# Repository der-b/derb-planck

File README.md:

# derb-planck

DIY mechanical keyboard which can be connected to several hosts at the same time.
[See blog post for more details.](https://der-b.com/posts/2024-05-08-mechanical-keyboard-derb-planck/)

## PCB

The PCB is designed with KiCad and is located in the subdirectory "PCB".

## Case

The Case is designed with FreeCAD and is located in the subdirectory "case".

## Firmeware

[This keyboard uses QMK as firmware.](https://github.com/der-b/qmk_firmware/tree/derb_planck/keyboards/handwired/derb_planck)

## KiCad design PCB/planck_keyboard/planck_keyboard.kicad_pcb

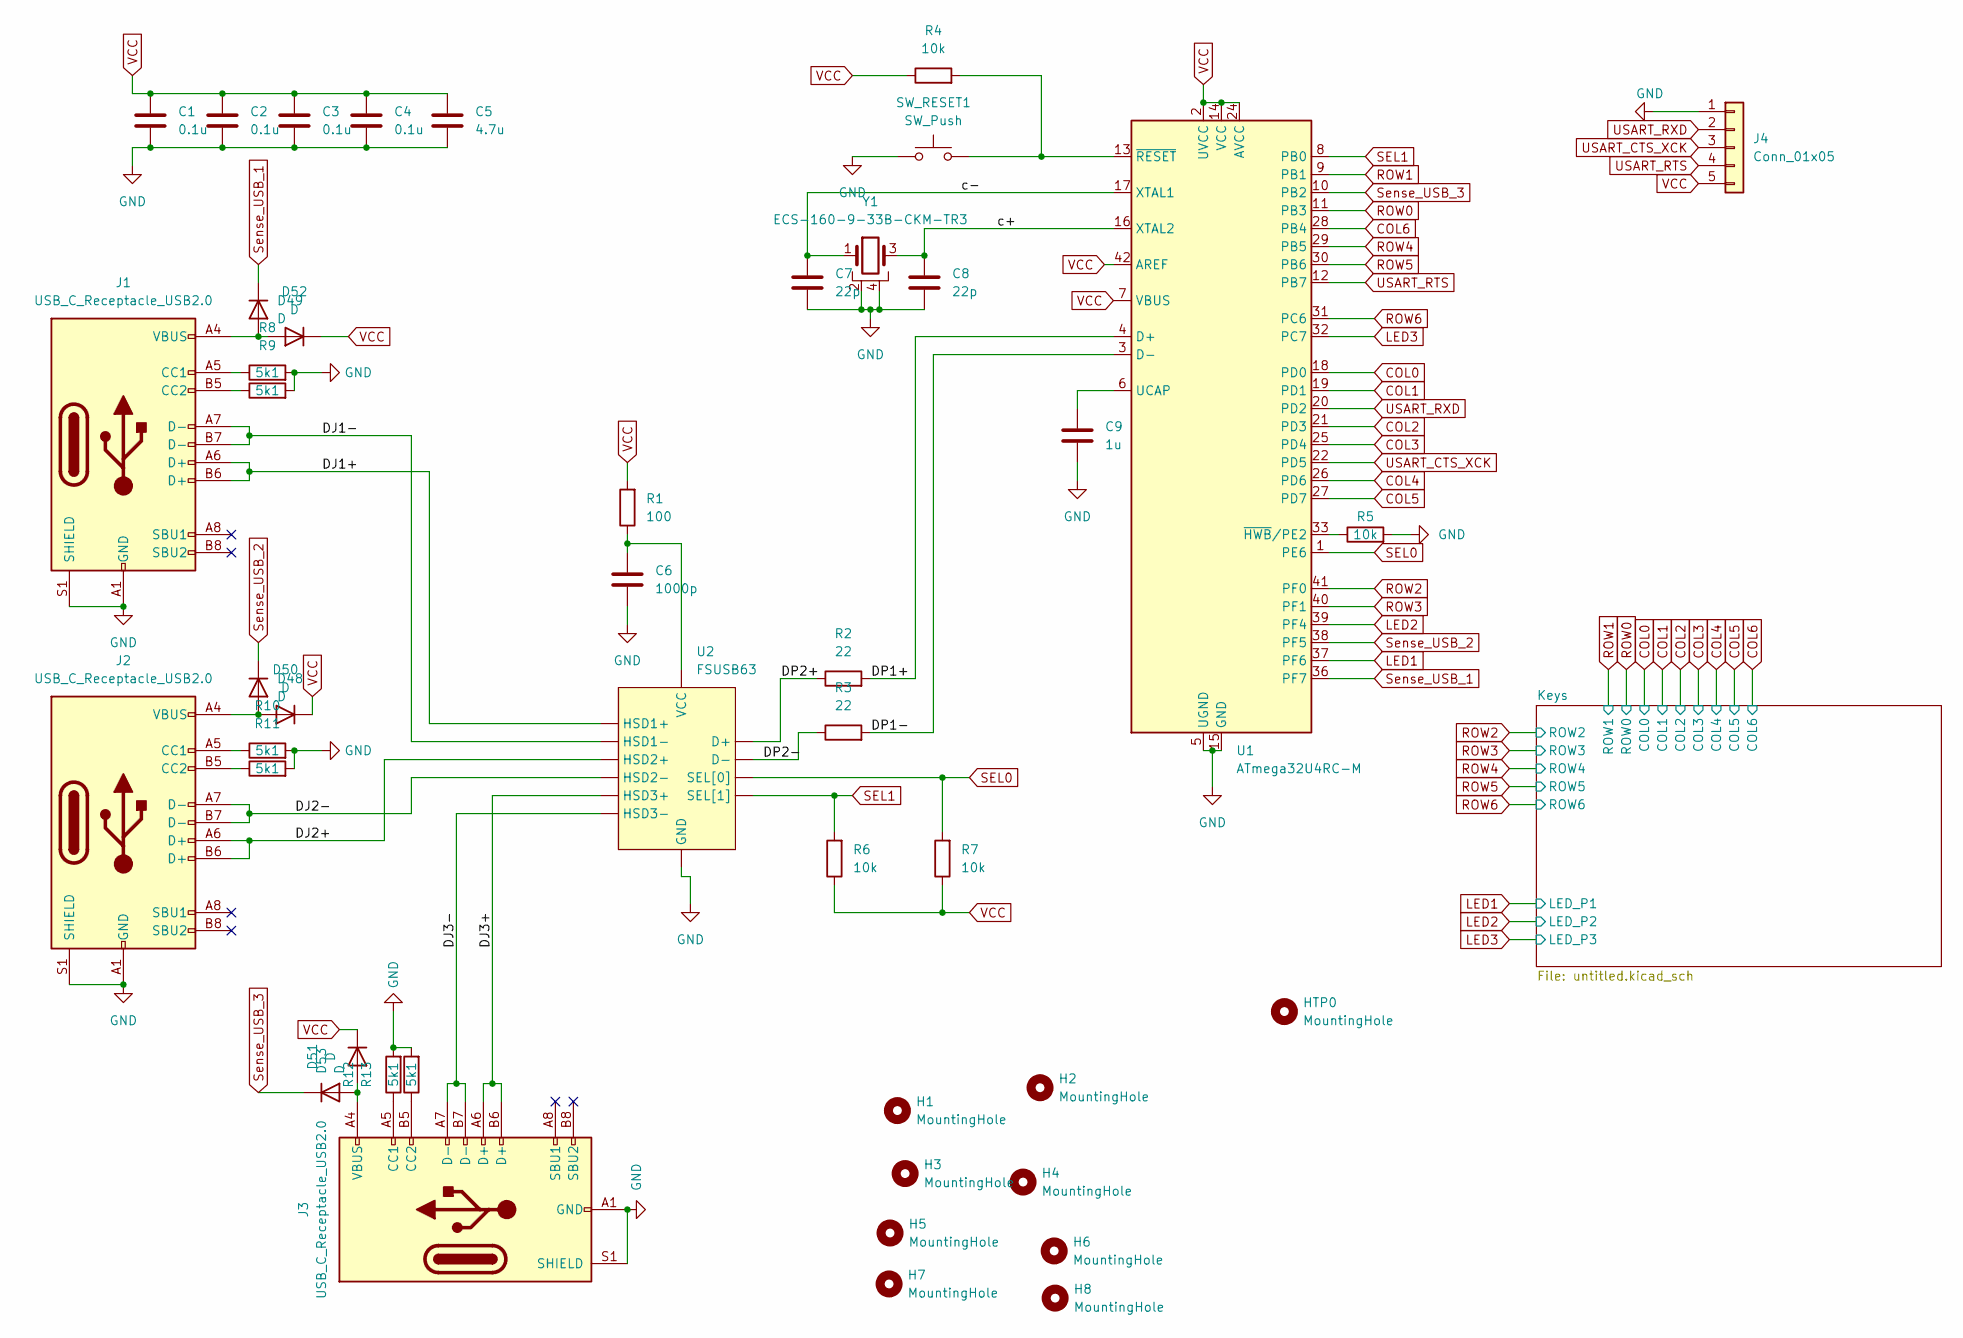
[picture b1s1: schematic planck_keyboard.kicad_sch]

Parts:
C1, C2, C3, C4: 0.1u; C_0603_1608Metric_Pad1.08x0.95mm_HandSolder
C5: 4.7u; C_0603_1608Metric_Pad1.08x0.95mm_HandSolder
C6: 1000p; C_0603_1608Metric_Pad1.08x0.95mm_HandSolder
C7, C8: 22p; C_0603_1608Metric_Pad1.08x0.95mm_HandSolder
C9: 1u; C_0603_1608Metric_Pad1.08x0.95mm_HandSolder
D48, D49, D50, D51, D52, D53: D; D_SOD-523
H1, H2, H3, H4, H5, H6, H7, H8: MountingHole; MountingHole_3.2mm_M3
HTP0: MountingHole; MountingHole_3.5mm
J1, J2, J3: USB_C_Receptacle_USB2.0; USB_C_Receptacle_HRO_TYPE-C-31-M-12
J4: Conn_01x05; PinHeader_1x05_P2.54mm_Vertical
R1: 100; R_0603_1608Metric_Pad0.98x0.95mm_HandSolder
R2, R3: 22; R_0603_1608Metric_Pad0.98x0.95mm_HandSolder
R4, R5, R6, R7: 10k; R_0603_1608Metric_Pad0.98x0.95mm_HandSolder
R8, R9, R10, R11, R12, R13: 5k1; R_0603_1608Metric_Pad0.98x0.95mm_HandSolder
SW_RESET1: SW_Push; SW_SPST_B3U-3000P
U1: ATmega32U4RC-M; QFN-44-1EP_7x7mm_P0.5mm_EP5.2x5.2mm
U2: FSUSB63
Y1: ECS-160-9-33B-CKM-TR3; Crystal_SMD_3225-4Pin_3.2x2.5mm_HandSoldering

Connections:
/DJ1+: J1.A6 (D+), J1.B6 (D+), U2.6 (HSD1+)
/DJ1-: J1.A7 (D-), J1.B7 (D-), U2.5 (HSD1-)
/DJ2+: J2.A6 (D+), J2.B6 (D+), U2.8 (HSD2+)
/DJ2-: J2.A7 (D-), J2.B7 (D-), U2.7 (HSD2-)
/DJ3+: J3.A6 (D+), J3.B6 (D+), U2.10 (HSD3+)
/DJ3-: J3.A7 (D-), J3.B7 (D-), U2.9 (HSD3-)
/DP1+: R2.2, U1.4 (D+)
/DP1-: R3.2, U1.3 (D-)
/DP2+: R2.1, U2.1 (D+)
/DP2-: R3.1, U2.2 (D-)
/c+: C8.1, U1.16 (XTAL2), Y1.3
/c-: C7.1, U1.17 (XTAL1), Y1.1
COL0: U1.18 (PD0); also elsewhere on the board
COL1: U1.19 (PD1); also elsewhere on the board
COL2: U1.21 (PD3); also elsewhere on the board
COL3: U1.25 (PD4); also elsewhere on the board
COL4: U1.26 (PD6); also elsewhere on the board
COL5: U1.27 (PD7); also elsewhere on the board
COL6: U1.28 (PB4); also elsewhere on the board
LED1: U1.37 (PF6); also elsewhere on the board
LED2: U1.39 (PF4); also elsewhere on the board
LED3: U1.32 (PC7); also elsewhere on the board
unnamed: D48.2 (A), D50.2 (A), J2.A4 (VBUS), J2.A9 (VBUS), J2.B4 (VBUS), J2.B9 (VBUS)
unnamed: D49.2 (A), D52.2 (A), J1.A4 (VBUS), J1.A9 (VBUS), J1.B4 (VBUS), J1.B9 (VBUS)
unnamed: D51.2 (A), D53.2 (A), J3.A4 (VBUS), J3.A9 (VBUS), J3.B4 (VBUS), J3.B9 (VBUS)
unnamed: J1.A5 (CC1), R8.1
unnamed: J1.B5 (CC2), R9.1
unnamed: J2.A5 (CC1), R10.1
unnamed: J2.B5 (CC2), R11.1
unnamed: J3.A5 (CC1), R12.1
unnamed: J3.B5 (CC2), R13.1
unnamed: C9.1, U1.6 (UCAP)
unnamed: R5.1, U1.33 (~HWB/PE2)
unnamed: R4.2, SW_RESET1.2, U1.13 (~RESET)
unnamed: C6.1, R1.1, U2.12 (VCC)
ROW0: U1.11 (PB3); also elsewhere on the board
ROW1: U1.9 (PB1); also elsewhere on the board
ROW2: U1.41 (PF0); also elsewhere on the board
ROW3: U1.40 (PF1); also elsewhere on the board
ROW4: U1.29 (PB5); also elsewhere on the board
ROW5: U1.30 (PB6); also elsewhere on the board
ROW6: U1.31 (PC6); also elsewhere on the board
SEL0: R7.2, U1.1 (PE6), U2.4 (SEL[0])
SEL1: R6.2, U1.8 (PB0), U2.11 (SEL[1])
Sense_USB_1: D49.1 (K), U1.36 (PF7)
Sense_USB_2: D48.1 (K), U1.38 (PF5)
Sense_USB_3: D53.1 (K), U1.10 (PB2)
USART_CTS_XCK: J4.3, U1.22 (PD5)
USART_RTS: J4.4, U1.12 (PB7)
USART_RXD: J4.2, U1.20 (PD2)
VCC: C1.1, C2.1, C3.1, C4.1, C5.1, D50.1 (K), D51.1 (K), D52.1 (K), J4.5, R1.2, R4.1, R6.1, R7.1, U1.2 (UVCC), U1.7 (VBUS), U1.14 (VCC), U1.24 (AVCC), U1.34 (VCC), U1.42 (AREF), U1.44 (AVCC)

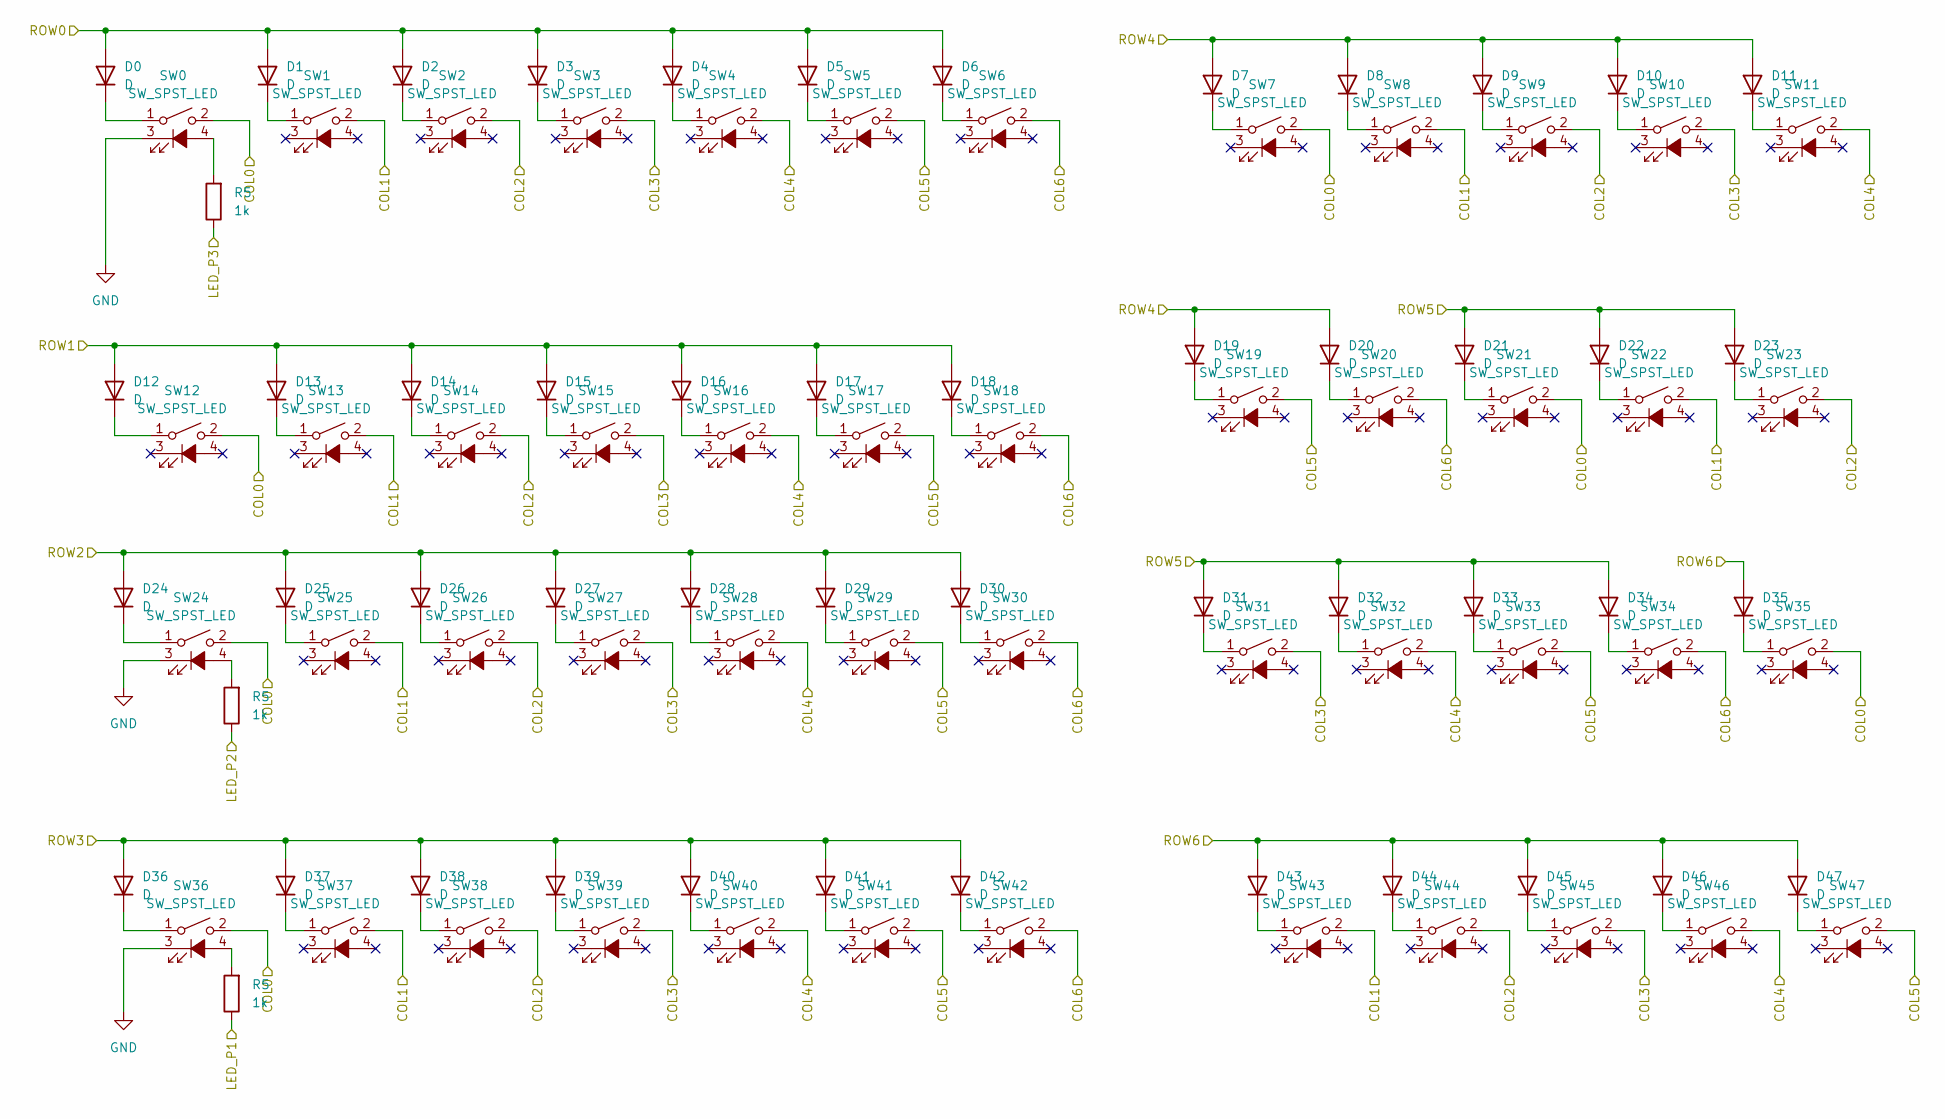
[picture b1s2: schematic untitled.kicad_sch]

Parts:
D0, D1, D2, D3, D4, D5, D6, D7, D8, D9, D10, D11, D12, D13, D14, D15, D16, D17, D18, D19, D20, D21, D22, D23, D24, D25, D26, D27, D28, D29, D30, D31, D32, D33, D34, D35, D36, D37, D38, D39, D40, D41, D42, D43, D44, D45, D46, D47: D; D_SOD-523
R5: 1k; R_0603_1608Metric_Pad0.98x0.95mm_HandSolder
SW0, SW1, SW2, SW3, SW4, SW5, SW6, SW7, SW8, SW9, SW10, SW11, SW12, SW13, SW14, SW15, SW16, SW17, SW18, SW19, SW20, SW21, SW22, SW23, SW24, SW25, SW26, SW27, SW28, SW29, SW30, SW31, SW32, SW33, SW34, SW35, SW36, SW37, SW38, SW39, SW40, SW41, SW42, SW43, SW44, SW45, SW46, SW47: SW_SPST_LED; SW_Cherry_MX_LowProfile_1.00u_PCB_V2

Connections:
COL0: SW0.2, SW7.2, SW12.2, SW21.2, SW24.2, SW35.2, SW36.2; also elsewhere on the board
COL1: SW1.2, SW8.2, SW13.2, SW22.2, SW25.2, SW37.2, SW43.2; also elsewhere on the board
COL2: SW2.2, SW9.2, SW14.2, SW23.2, SW26.2, SW38.2, SW44.2; also elsewhere on the board
COL3: SW3.2, SW10.2, SW15.2, SW27.2, SW31.2, SW39.2, SW45.2; also elsewhere on the board
COL4: SW4.2, SW11.2, SW16.2, SW28.2, SW32.2, SW40.2, SW46.2; also elsewhere on the board
COL5: SW5.2, SW17.2, SW19.2, SW29.2, SW33.2, SW41.2, SW47.2; also elsewhere on the board
COL6: SW6.2, SW18.2, SW20.2, SW30.2, SW34.2, SW42.2; also elsewhere on the board
unnamed: D0.1 (K), SW0.1
unnamed: D1.1 (K), SW1.1
unnamed: D2.1 (K), SW2.1
unnamed: D3.1 (K), SW3.1
unnamed: D4.1 (K), SW4.1
unnamed: D5.1 (K), SW5.1
unnamed: D6.1 (K), SW6.1
unnamed: D7.1 (K), SW7.1
unnamed: D8.1 (K), SW8.1
unnamed: D9.1 (K), SW9.1
unnamed: D10.1 (K), SW10.1
unnamed: D11.1 (K), SW11.1
unnamed: D12.1 (K), SW12.1
unnamed: D13.1 (K), SW13.1
unnamed: D14.1 (K), SW14.1
unnamed: D15.1 (K), SW15.1
unnamed: D16.1 (K), SW16.1
unnamed: D17.1 (K), SW17.1
unnamed: D18.1 (K), SW18.1
unnamed: D19.1 (K), SW19.1
unnamed: D20.1 (K), SW20.1
unnamed: D21.1 (K), SW21.1
unnamed: D22.1 (K), SW22.1
unnamed: D23.1 (K), SW23.1
unnamed: D24.1 (K), SW24.1
unnamed: D25.1 (K), SW25.1
unnamed: D26.1 (K), SW26.1
unnamed: D27.1 (K), SW27.1
unnamed: D28.1 (K), SW28.1
unnamed: D29.1 (K), SW29.1
unnamed: D30.1 (K), SW30.1
unnamed: D31.1 (K), SW31.1
unnamed: D32.1 (K), SW32.1
unnamed: D33.1 (K), SW33.1
unnamed: D34.1 (K), SW34.1
unnamed: D35.1 (K), SW35.1
unnamed: D36.1 (K), SW36.1
unnamed: D37.1 (K), SW37.1
unnamed: D38.1 (K), SW38.1
unnamed: D39.1 (K), SW39.1
unnamed: D40.1 (K), SW40.1
unnamed: D41.1 (K), SW41.1
unnamed: D42.1 (K), SW42.1
unnamed: D43.1 (K), SW43.1
unnamed: D44.1 (K), SW44.1
unnamed: D45.1 (K), SW45.1
unnamed: D46.1 (K), SW46.1
unnamed: D47.1 (K), SW47.1
unnamed 80: R5.1; also elsewhere on the board
ROW0: D0.2 (A), D1.2 (A), D2.2 (A), D3.2 (A), D4.2 (A), D5.2 (A), D6.2 (A); also elsewhere on the board
ROW1: D12.2 (A), D13.2 (A), D14.2 (A), D15.2 (A), D16.2 (A), D17.2 (A), D18.2 (A); also elsewhere on the board
ROW2: D24.2 (A), D25.2 (A), D26.2 (A), D27.2 (A), D28.2 (A), D29.2 (A), D30.2 (A); also elsewhere on the board
ROW3: D36.2 (A), D37.2 (A), D38.2 (A), D39.2 (A), D40.2 (A), D41.2 (A), D42.2 (A); also elsewhere on the board
ROW4: D7.2 (A), D8.2 (A), D9.2 (A), D10.2 (A), D11.2 (A), D19.2 (A), D20.2 (A); also elsewhere on the board
ROW5: D21.2 (A), D22.2 (A), D23.2 (A), D31.2 (A), D32.2 (A), D33.2 (A), D34.2 (A); also elsewhere on the board
ROW6: D35.2 (A), D43.2 (A), D44.2 (A), D45.2 (A), D46.2 (A), D47.2 (A); also elsewhere on the board

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
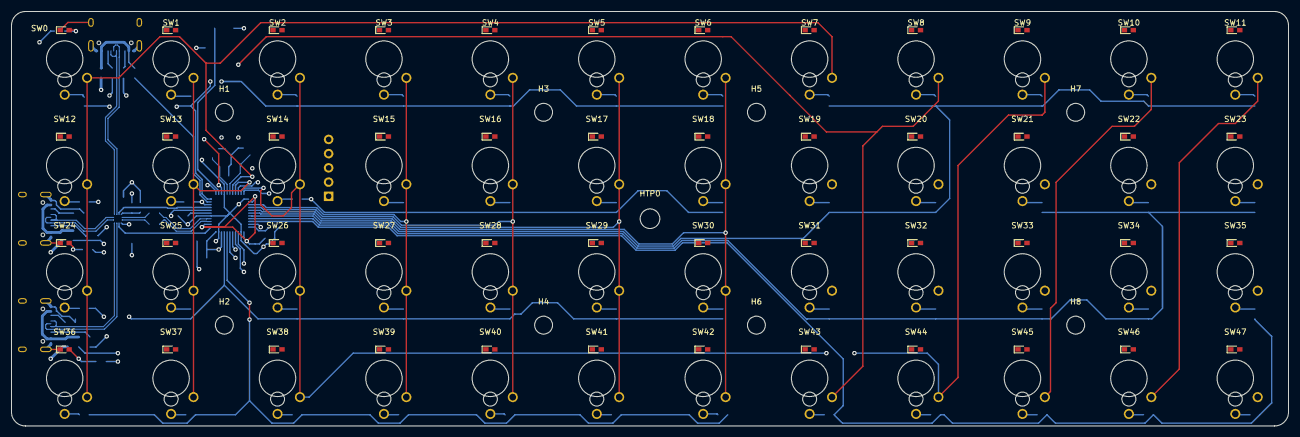
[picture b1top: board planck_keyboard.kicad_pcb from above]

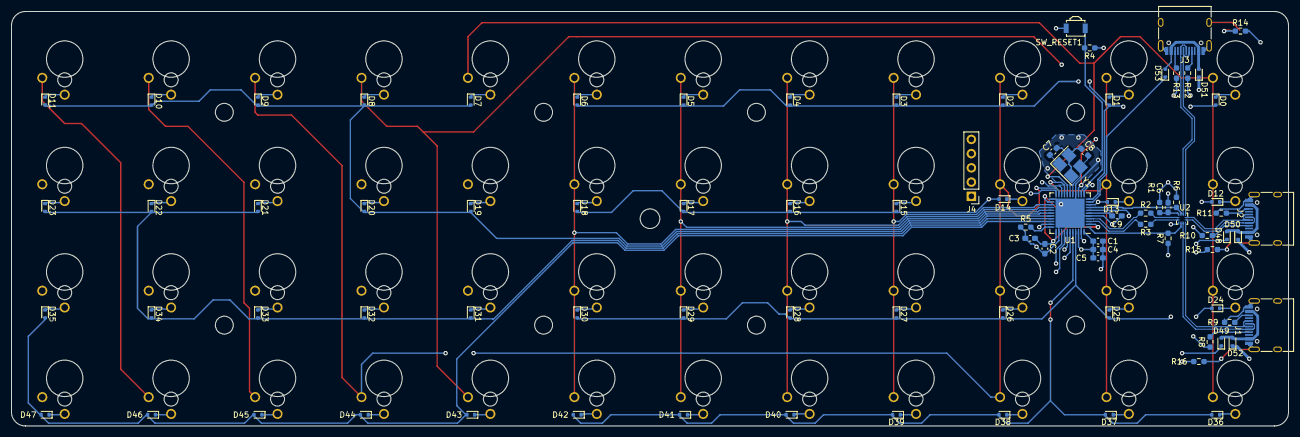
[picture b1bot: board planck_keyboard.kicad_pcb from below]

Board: 4 copper layers, 228.0 x 74.0 mm, 144 parts (87 on the bottom side), 103 nets.

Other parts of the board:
R14, R15, R16: 1k; R_0603_1608Metric_Pad0.98x0.95mm_HandSolder

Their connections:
LED1: R16.1; also elsewhere on the board
LED2: R15.1; also elsewhere on the board
LED3: R14.1; also elsewhere on the board

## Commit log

2024-05-08 Initial commit.
